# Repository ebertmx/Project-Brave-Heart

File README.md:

# Project Brave Heart

 Project Brave Heart is a radio alarm clock assembly. This model is turtle themed and features a wheeled drive system which activates upon the alarm being triggered - causing the turtle to run away. The main components include a custom PCB, a raspberry pi Pico, and a RDA5807M radio module. A complete description and documentation can be found in this repository.

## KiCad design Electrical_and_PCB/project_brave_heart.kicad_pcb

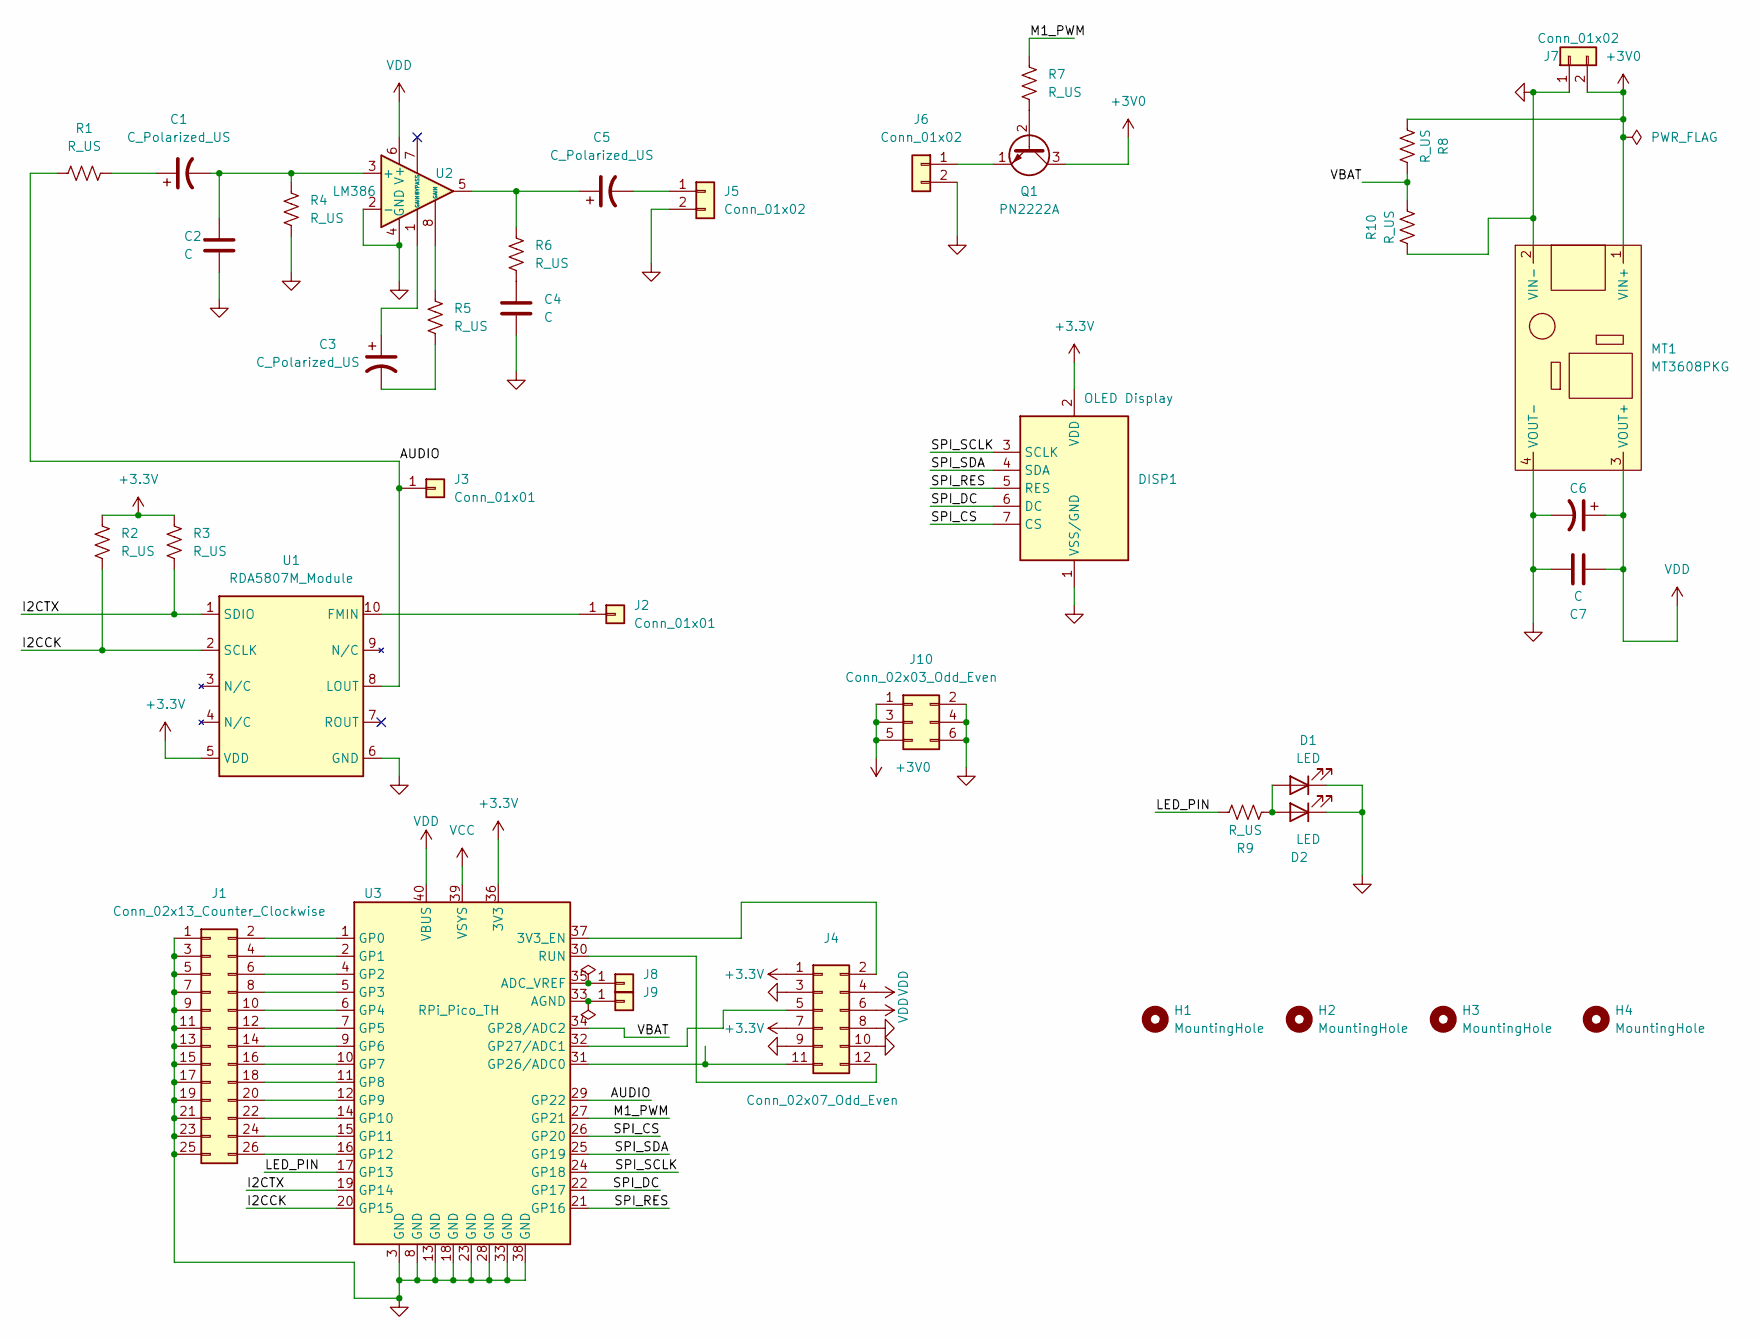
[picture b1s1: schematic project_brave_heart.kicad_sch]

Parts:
C1, C3, C5, C6: C_Polarized_US; CP_Radial_D6.3mm_P2.50mm
C2, C4, C7: C; C_Axial_L3.8mm_D2.6mm_P10.00mm_Horizontal
D1, D2: LED; PinHeader_1x02_P2.54mm_Vertical
DISP1: OLED Display; PinHeader_1x07_P2.54mm_Vertical
H1, H2, H3, H4: MountingHole; MountingHole_3.2mm_M3_Pad
J1: Conn_02x13_Counter_Clockwise; PinHeader_2x13_P2.54mm_Vertical
J2: Conn_01x01; MountingHole_3.2mm_M3_Pad_Via
J3, J8, J9: Conn_01x01; PinHeader_1x01_P2.54mm_Vertical
J4: Conn_02x07_Odd_Even; PinHeader_2x06_P2.54mm_Vertical
J5, J6, J7: Conn_01x02; TerminalBlock_Phoenix_MKDS-1,5-2_1x02_P5.00mm_Horizontal
J10: Conn_02x03_Odd_Even; PinHeader_2x03_P2.54mm_Vertical
MT1: MT3608PKG
Q1: PN2222A; TO-92_Inline_Wide
R1, R2, R3, R4, R5, R6, R7, R8, R9, R10: R_US; R_Axial_DIN0207_L6.3mm_D2.5mm_P10.16mm_Horizontal
U1: RDA5807M_Module; RDA5807M_Module_TH
U2: LM386; DIP-8_W7.62mm
U3: RPi_Pico_TH

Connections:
+3V0: J7.2, J10.1, J10.3, J10.5, MT1.1 (VIN+), Q1.3 (C), R8.2
+3V3: DISP1.2 (VDD), J4.1, J4.7, R2.1, R3.1, U1.5 (VDD), U3.36 (3V3)
/AUDIO: J3.1, R1.1, U1.8 (LOUT), U3.29 (GP22)
/I2CCK: R2.2, U1.2 (SCLK), U3.20 (GP15)
/I2CTX: R3.2, U1.1 (SDIO), U3.19 (GP14)
/LED_PIN: R9.1, U3.17 (GP13)
/M1_PWM: R7.1, U3.27 (GP21)
/SPI_CS: DISP1.7 (CS), U3.26 (GP20)
/SPI_DC: DISP1.6 (DC), U3.22 (GP17)
/SPI_RES: DISP1.5 (RES), U3.21 (GP16)
/SPI_SCLK: DISP1.3 (SCLK), U3.24 (GP18)
/SPI_SDA: DISP1.4 (SDA), U3.25 (GP19)
/VBAT: R8.1, R10.1, U3.34 (GP28/ADC2)
unnamed: C1.1, R1.2
unnamed: C1.2, C2.1, R4.1, U2.3 (+)
unnamed: C3.1, U2.1 (GAIN)
unnamed: C3.2, R5.2
unnamed: C4.1, R6.2
unnamed: C5.1, R6.1, U2.5
unnamed: C5.2, J5.1
unnamed: D1.2 (A), D2.2 (A), R9.2
unnamed: J1.2, U3.1 (GP0)
unnamed: J1.4, U3.2 (GP1)
unnamed: J1.6, U3.4 (GP2)
unnamed: J1.8, U3.5 (GP3)
unnamed: J1.10, U3.6 (GP4)
unnamed: J1.12, U3.7 (GP5)
unnamed: J1.14, U3.9 (GP6)
unnamed: J1.16, U3.10 (GP7)
unnamed: J1.18, U3.11 (GP8)
unnamed: J1.20, U3.12 (GP9)
unnamed: J1.22, U3.14 (GP10)
unnamed: J1.24, U3.15 (GP11)
unnamed: J1.26, U3.16 (GP12)
unnamed: J2.1, U1.10 (FMIN)
unnamed: J6.1, Q1.1 (E)
unnamed: J8.1, U3.35 (ADC_VREF)
unnamed: Q1.2 (B), R7.2
unnamed: R5.1, U2.8 (GAIN)
unnamed: J4.12, U3.30 (RUN)
unnamed: J4.11, U3.31 (GP26/ADC0)
unnamed: J4.5, U3.32 (GP27/ADC1)
unnamed: J4.2, U3.37 (3V3_EN)
VCC: U3.39 (VSYS)
VDD: C6.1, C7.2, J4.4, J4.6, MT1.3 (VOUT+), U2.6 (V+), U3.40 (VBUS)

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
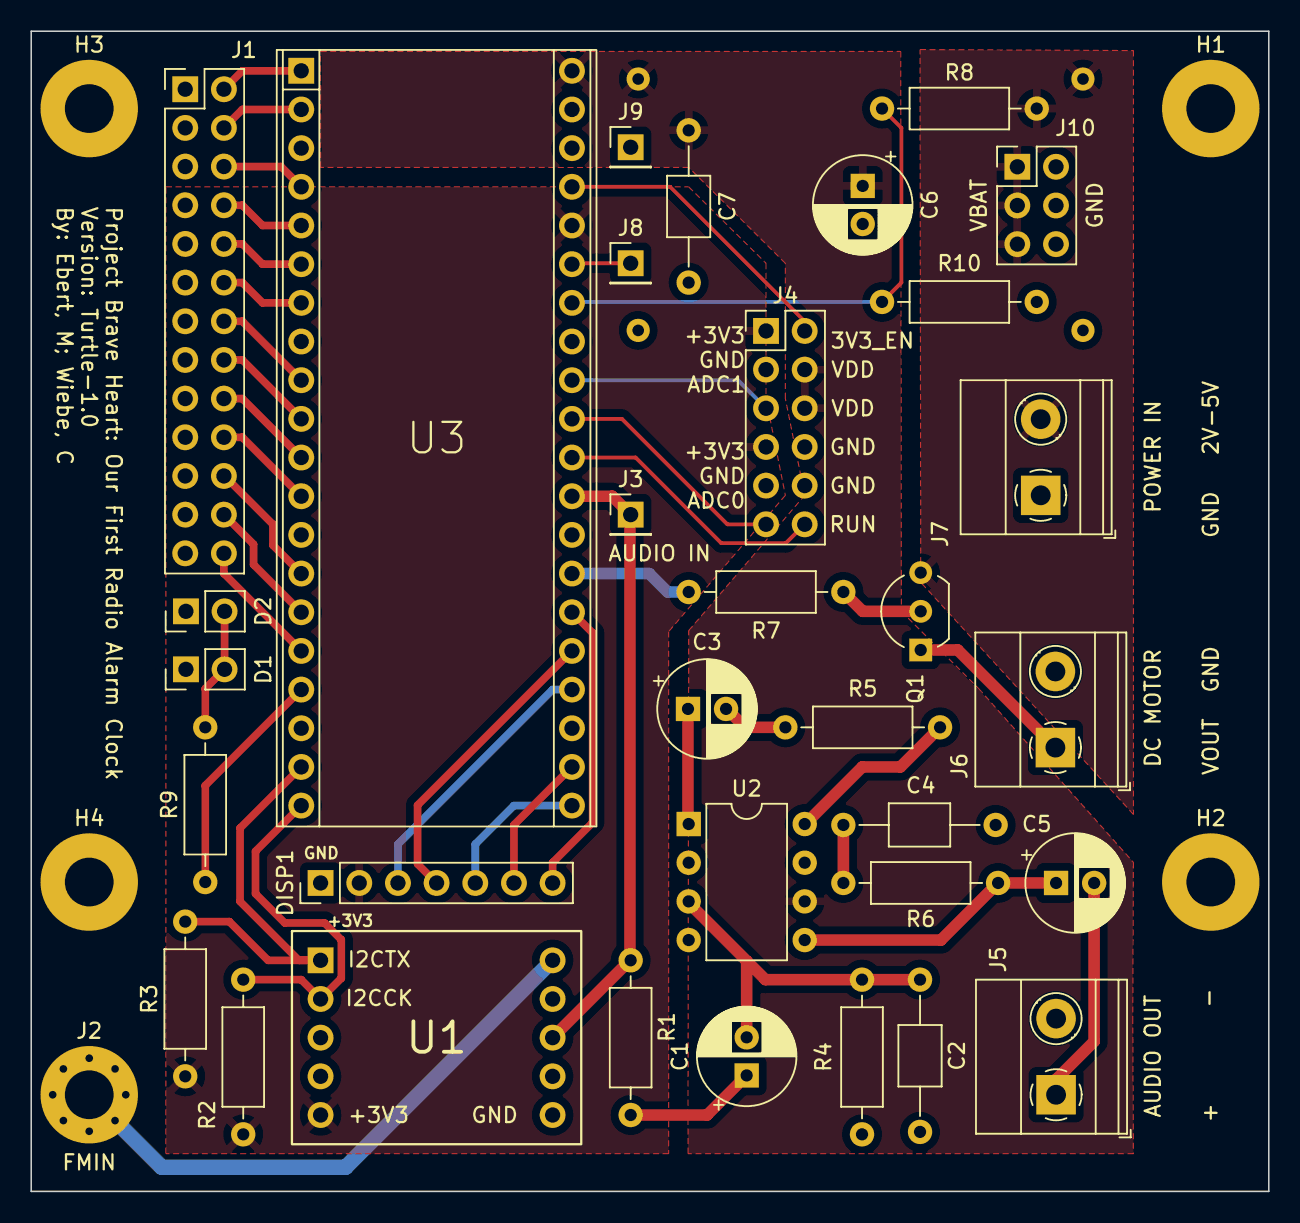
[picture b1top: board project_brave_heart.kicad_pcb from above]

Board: 2 copper layers, 81.3 x 76.2 mm, 39 parts (1 on the bottom side), 45 nets.

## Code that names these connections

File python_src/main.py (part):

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SCREEN_WIDTH = 128 #number of columns
SCREEN_HEIGHT = 64 #number of rows
spi_sck = Pin(18) # sck stands for serial clock; always be connected to SPI SCK pin of the Pico
spi_sda = Pin(19) # sda stands for serial data;  always be connected to SPI TX pin of the Pico; this is the MOSI
spi_res = Pin(16) # res stands for reset; always be connected to SPI RX pin of the Pico; this is the MISO
spi_dc  = Pin(17) # dc stands for data/commonda; always be connected to SPI CSn pin of the Pico
spi_cs  = Pin(20) # can be connected to any free GPIO pin of the Pico
SPI_DEVICE = 0 
oled_spi = SPI( SPI_DEVICE, baudrate= 100000, sck= spi_sck, mosi= spi_sda )
oled = SSD1306_SPI( SCREEN_WIDTH, SCREEN_HEIGHT, oled_spi, spi_dc, spi_res, spi_cs, True )
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
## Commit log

2022-09-12 Created Repo from local files
2023-02-11 UpdatedReport
2023-03-06 Update Documents
